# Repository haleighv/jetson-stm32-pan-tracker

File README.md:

# Jetson Orin + STM32H7 closed-loop visual tracker

> Status: in progress (started October 2026).

A camera mounted to a motor for visually tracking and centering an AprilTag (pan-only).

Vision in ROS 2 runs on a **Jetson Orin Nano**, while an **STM32H723** controls a geared DC motor in a 1 kHz closed loop. The real-time MCU communicates with the Jetson via **CAN**, with bulk telemetry handled over **Ethernet**. The motor control loop runs independently of the Linux and ROS 2 timing on the Jetson, and disables the motor if the Jetson stops responding.

Safety:
- hardware e-stop
- firmware state machine
- heartbeat timeout
- current limiting
- watchdog timer

## Progress
- [x] Jetson: JetPack 7.2.1 + ROS 2 Jazzy, IMX219 at 720p60 (59.77 fps, 0 dropped over ~68 s)
- [x] PID controller with host unit tests (anti-windup, no derivative kick, NaN-safe config)
- [x] STM32 bring-up: 520 MHz, FreeRTOS, task table, queued leveled logging, UART CLI
- [x] STM32 task framework: pub/sub messaging, startup sync, supervisor skeleton, LED task
- [x] 1 kHz control tick on TIM6: ±153 ns jitter under load (DWT min/max)
- [x] Jitter p99 from a Saleae capture: 77 ns idle, 34 ns loaded (crystal clock)
- [x] FDCAN internal loopback: 1M frames, 0 lost, 0 errors
- [x] CI: host tests + firmware build on every push, elf/map kept per commit
- [x] CAN bus to the Jetson at 1 Mbps: both directions, 0 errors
- [x] Motor open loop: VNH5019 driver, encoder, current sense, latched fault interrupt, brake on stop (220 RPM at full duty, stops in ~37 ms)
- [x] Motor driven from the 1 kHz control tick: single writer, lock-free task requests, 2 ms reversal brake, ~2 µs per tick
- [x] Custom Nucleo shield (Nuc-hatch rev A): designed in KiCad, ordered assembled from JLCPCB
- [ ] Motor closed loop: velocity and position
- [ ] Safety: e-stop, heartbeat, watchdog
- [ ] ROS 2 tracking pipeline
- [ ] Measured results

## Demo
Coming soon

## Results
| Metric | Target (Day 0 estimate) | Measured |
|---|---|---|
| Photon-to-motion latency, p50 / p90 | < 60 / 80 ms | TBD |
| Control-loop period jitter, p99 | < 2 µs | 77 ns idle, 34 ns loaded (Saleae, 90 s) |
| Step response (30°): rise time / overshoot | < 100 ms / < 10 % | TBD |
| Heartbeat-loss → motor disabled | ≤ 50 ms | TBD |

## Architecture (planned)
```mermaid
flowchart LR
  subgraph J[Jetson Orin Nano · JetPack 7.2.1 · ROS 2 Jazzy]
    CAM[camera node<br/>IMX219 720p60] --> TAG[apriltag node]
    TAG --> TRK[tracker node<br/>outer loop 60 Hz]
    TRK --> BR[can_bridge<br/>SocketCAN]
    LOG[telemetry logger]
  end
  BR -- "CAN 1 Mbps: setpoint, heartbeat, command" --> M
  M -- "CAN: status 100 Hz" --> BR
  M -- "UDP: 1 kHz telemetry" --> LOG
  subgraph M[NUCLEO-H723ZG · FreeRTOS]
    SAFE[safety state machine] --> CTL[pos→vel PID 1 kHz]
    CTL --> PWM[PWM 20 kHz + current limit]
    DBG[logs + CLI<br/>USART3]
  end
  PWM --> DRV[VNH5019] --> MOT[goBILDA 5203 gearmotor]
  MOT -- encoder --> CTL
  DRV -- current sense --> PWM
  ES[e-stop] -- "cuts 12 V" --> DRV
  ES -- sense --> SAFE
```

## Repo layout
```
firmware/
  lib/        portable C, host-tested (PID, CLI parser, LED fade)
  tests/      Unity host tests
  nucleo/     NUCLEO-H723ZG target: CubeMX BSP (Core/, Drivers/, .ioc) + app/
  scripts/    build.sh, test.sh (host), build_nucleo.sh, flash.sh (target)
ros2_ws/      ROS 2 packages (camera, apriltag, tracker, can_bridge)
hardware/     wiring, pinouts, CAD (STEP/3MF), photos
docs/         plan, worklog, firmware architecture, results/
tools/        analysis scripts (jitter, step response, latency)
```

## Build and test
Needs cmake, ninja, Arm GNU Toolchain (`arm-none-eabi-gcc`), and STM32CubeProgrammer (`STM32_Programmer_CLI` on PATH).

```
./firmware/scripts/test.sh            # host unit tests (PID, CLI, LED fade)
./firmware/scripts/flash.sh           # build + flash the Nucleo over ST-LINK
tio -b 1000000 /dev/cu.usbmodem*      # logs + CLI at 1 Mbaud, type ? for commands
python3 tools/motor_profile.py        # motor characterization suite (quit tio first)
```

CI (`.github/workflows/ci.yml`) runs the host tests and builds the firmware on every push to `mainline` and every PR. Each run keeps `nucleo.elf` and `nucleo.map` as a download. To flash one:
```
STM32_Programmer_CLI -c port=SWD -w nucleo.elf -v -rst
```

### Debugging in VS Code
Open the repo folder and install the recommended extensions when prompted (`.vscode/extensions.json`): Cortex-Debug, RTOS Views, STM32Cube for VS Code (provides the ST-LINK GDB server, STM32CubeProgrammer, and the STM32H7 device pack), CMake Tools.

| Key | Does |
|---|---|
| `Cmd + Shift + B` | Build the Nucleo firmware (`.vscode/tasks.json`) |
| `F5` | Build, flash, debug, stop at `main()` (`.vscode/launch.json`, "Debug nucleo") |

"Attach nucleo" connects to a running board without reflashing or resetting, for looking at a hang or fault.

Tool versions the debug config expects: ST-LINK GDB server 7.14.0, STM32CubeProgrammer 2.23.0, STM32H7xx DFP 1.3.0 (paths under `~/Library/Application Support/stm32cube/`). If an extension update changes them, find the new paths with `mdfind -name ST-LINK_gdbserver` (and `STM32_Programmer_CLI`, `STM32H723.svd`) and update `launch.json`.

Optional shortcuts, in your own keybindings (`Cmd + Shift + P` → Preferences: Open Keyboard Shortcuts (JSON)):
```json
{ "key": "f6",          "command": "workbench.action.tasks.runTask", "args": "flash nucleo" },
{ "key": "cmd+shift+t", "command": "workbench.action.tasks.runTask", "args": "host tests" }
```
`F6` replaces VS Code's "Focus Next Part" and `Cmd + Shift + T` replaces "Reopen Closed Editor".

## Docs
- [Plan](docs/plan.md): milestones, results targets, scope
- [Worklog](docs/worklog.md): day-by-day progress
- [Firmware architecture](docs/firmware-architecture.md): tasks, priorities, logging, memory
- [Results](docs/results/): raw measurements
- [CAN wiring](hardware/can-wiring.md): bus layout, pins on both ends, checks
- [CAD](hardware/cad/): 3D-printed enclosure for the motor driver (STEP, 3MF)
- [Pinouts](hardware/pinouts.html): Nucleo Zio headers and Jetson 40-pin, with this project's pins marked (open locally in a browser)

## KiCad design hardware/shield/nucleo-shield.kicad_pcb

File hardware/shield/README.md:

# Nuc-hatch: Nucleo-H723ZG shield, rev A

A shield for the NUCLEO-H723ZG that replaces the hand-soldered jumper hub: CAN module socket, VNH5019 and encoder headers, sensor and end-of-travel inputs, an e-stop with a hardware path to the driver's EN line, and a breakout header that can cut and probe every signal. All through-hole, 2.54 mm headers, 2 layers.

Status: routed (Freerouting, then cleaned up in KiCad 10). ERC clean. DRC clean, with three courtyard overlaps excluded (Nucleo mounting holes next to the Zio rows, as on the Nucleo itself). Ordered 2026-11-18 from JLCPCB: 5 boards, fully assembled (top and bottom). Not tested yet.

## Files

| File | What |
|---|---|
| `nucleo-shield.kicad_pro`, `.kicad_sch`, `.kicad_pcb` | KiCad project, now saved by KiCad 10. |
| `gen/spec.py` | Source of truth: parts, nets, footprints, placement. |
| `gen/gen_sch.py`, `gen/gen_pcb.py`, `gen/gen_bom.py` | Generate the schematic, the placed board and `BOM.csv` from the spec. |
| `gen/check_net.py` | Compares the schematic's netlist with the spec. |
| `nucleo-shield-top.png`, `nucleo-shield-bottom.png` | KiCad 3D renders of the routed board. |
| `schematic.pdf` | Schematic. |
| `fit-check-1to1.pdf` | Copper, silkscreen and outline at 1:1, for the paper fit check. |
| `art/nuc-hatch-silk.png`, `art/nuc-hatch-pixel-art.png` | Nuthatch logo: 1-bit silkscreen image (0.5 mm per pixel, 24.5 x 11 mm) and the colour pixel art it came from. |
| `BOM.csv` | Parts list, with the LCSC part numbers used for the JLCPCB assembly. |
| `nucleo-shield-revA-gerbers.zip` | Gerbers and drill files as ordered (KiCad 10 plot, Protel extensions). |
| `jlc/nucleo-shield-revA-bom-jlc.csv`, `jlc/nucleo-shield-revA-cpl-jlc.csv` | JLCPCB assembly BOM and placement. CN7-CN10 are bottom side; C2 and C3 are not fitted. |

Once the board is routed in KiCad, the KiCad files are the source; the generators are for rev A only.

## Zio geometry

- The Nucleo's mounting holes are the Arduino Uno holes (UM2407 Figure 6: 48.26, 50.80 and 15.24 mm spacings), so the Arduino rows come from KiCad's `Module:Arduino_UNO_R3`.
- Each Zio connector adds a second row one 2.54 mm column inward. Left side: odd pins outer. Right side: even pins outer. Pin 1 at the ST-LINK end.
- CN7 sits 4.06 mm off the 2.54 mm grid from CN10 (the Arduino D7/D8 gap). CN9 and CN10 end on the same row.
- Origin in `spec.py` is CN8 pin 1. Holes at (0, -13.97), (48.26, -12.70), (33.02, 38.10), (1.27, 62.23), (46.99, 62.23).

## Connectors

| Ref | Name | Pins | Goes to |
|---|---|---|---|
| J1 | MOTOR | 3V3, GND, INA, INB, PWM, ENA, ENB, CS | VNH5019 carrier logic side. ENA and ENB are tied on the board. |
| J2 | ENCODER | GND, 3V3, A, B | goBILDA 5203 encoder, through the breakout and R2/R3 (100 Ω) to PD12/PD13 |
| J3 | CAN | 3V3, GND, TX, RX | SN65HVD230 module (TX to its D, RX to its R) |
| J4 | HOME | 3V3, GND, SIG | Slot sensor, PD14 (TIM4 CH3, input capture) |
| J5, J6 | END+, END- | 3V3, GND, SIG | End-of-travel sensors, PF3 and PG1 |
| J7 | AUX | 3V3, GND, SIG | Spare, PD15 (TIM4 CH4) |
| J8 | ESTOP | SW, GND | Normally closed e-stop switch, PG12 through R5 |
| J9 | BREAKOUT | 2x15, left: device side, right: MCU side | One row per signal: ESTOP, HOME, END+, END-, AUX, PWM, INA, INB, EN, CS, ENC A, ENC B, CAN TX, CAN RX, SCOPE (PG14, both pins). A shunt across each row makes the normal connection. |
| J10 | POWER | 5V, 3V3, GND, GND | Meter and spare power |
| J11-J14 | GND | 2 pins each | Probe grounds, one in each corner |
| JP1, JP2 | STOP END+/- | shunt | Shunt fitted: that end sensor also cuts EN in hardware |

Motor current sense: R1 1 kΩ and C1 100 nF between the breakout's CS row and PF4 (corner about 1.6 kHz), same as the hub.

## Breakout

- Normal running: a shunt on all 14 signal rows (SCOPE needs none).
- Pull a shunt to isolate a device from the Nucleo, then probe either side, or drive the Nucleo side from outside.
- Open-top (tall) shunts leave the pin tips exposed, so probe hooks can clip on with the shunt fitted.
- With a shunt pulled, that Nucleo input floats unless firmware turns on its pull-up.

## Hardware stop

- The e-stop switch (normally closed) holds ESTOP_SW low. An open switch or a broken wire lets R4 pull it high.
- ESTOP_SW and the end sensors (high when blocked, through JP1/JP2) are diode-ORed (D1-D3) into Q1's base. Q1 pulls EN low, the VNH5019 turns off, and the firmware sees the line low with EN released, which latches the motor fault.
- The whole stop path sits on the device side of the breakout, so it still works with the breakout shunts pulled.
- R7 keeps Q1 off when every input is low.
- No e-stop wired: put a shunt on J8, or the driver stays off.

## Before ordering

1. Run ERC and DRC. Expected: clean, with the three courtyard overlaps between Zio headers and Nucleo mounting holes excluded.
2. Print `fit-check-1to1.pdf` at 100% (no fit-to-page), check the scale with a ruler, push the paper onto the Nucleo's Zio sockets, and check every pin lines up.
3. Check the J1 order against the Pololu carrier's silkscreen. I wire it with jumpers, so the order only has to match the labels.
4. Zio sockets need male headers with standard 6 mm mating pins. CN7-CN10 go in from the bottom (plastic under the board, long pins down; outlines and labels are on the bottom silkscreen) and solder on top. Solder them with the shield plugged into the Nucleo so they come out straight. Their footprints differ from the library copies for this reason (DRC warning excluded).

## Routing

- Freerouting (KiCad Plugin and Content Manager), then the session imported and fixed by hand: two GND pins on CN10 tied back to the pour.
- Rules: 0.3 mm tracks, 0.2 mm clearance, 0.6/0.3 mm vias. Relaxed to fab limits where the router squeezed: 0.15 mm minimum track (four short necks), 0.3 mm copper to edge, one thermal spoke allowed on crowded GND header pins.
- +3V3 ended up at 0.3 mm (0.225 mm in places): the Power net class pattern was `+3V3` but KiCad names the net `/+3V3`, so it never applied. Fine for the ~100 mA on 3.3 V.

## Regenerate

```
cd hardware/shield/gen
python3 gen_sch.py ../nucleo-shield.kicad_sch
python3 gen_pcb.py place ../nucleo-shield.kicad_pcb
python3 gen_bom.py > ../BOM.csv
```

`gen_pcb.py` overwrites the board, routing included. Needs KiCad's Python module (`pcbnew`) and `sexpdata`.

Author: Haleigh (haleighv). Copyright (c) 2026 haleighv. SPDX-License-Identifier: MIT

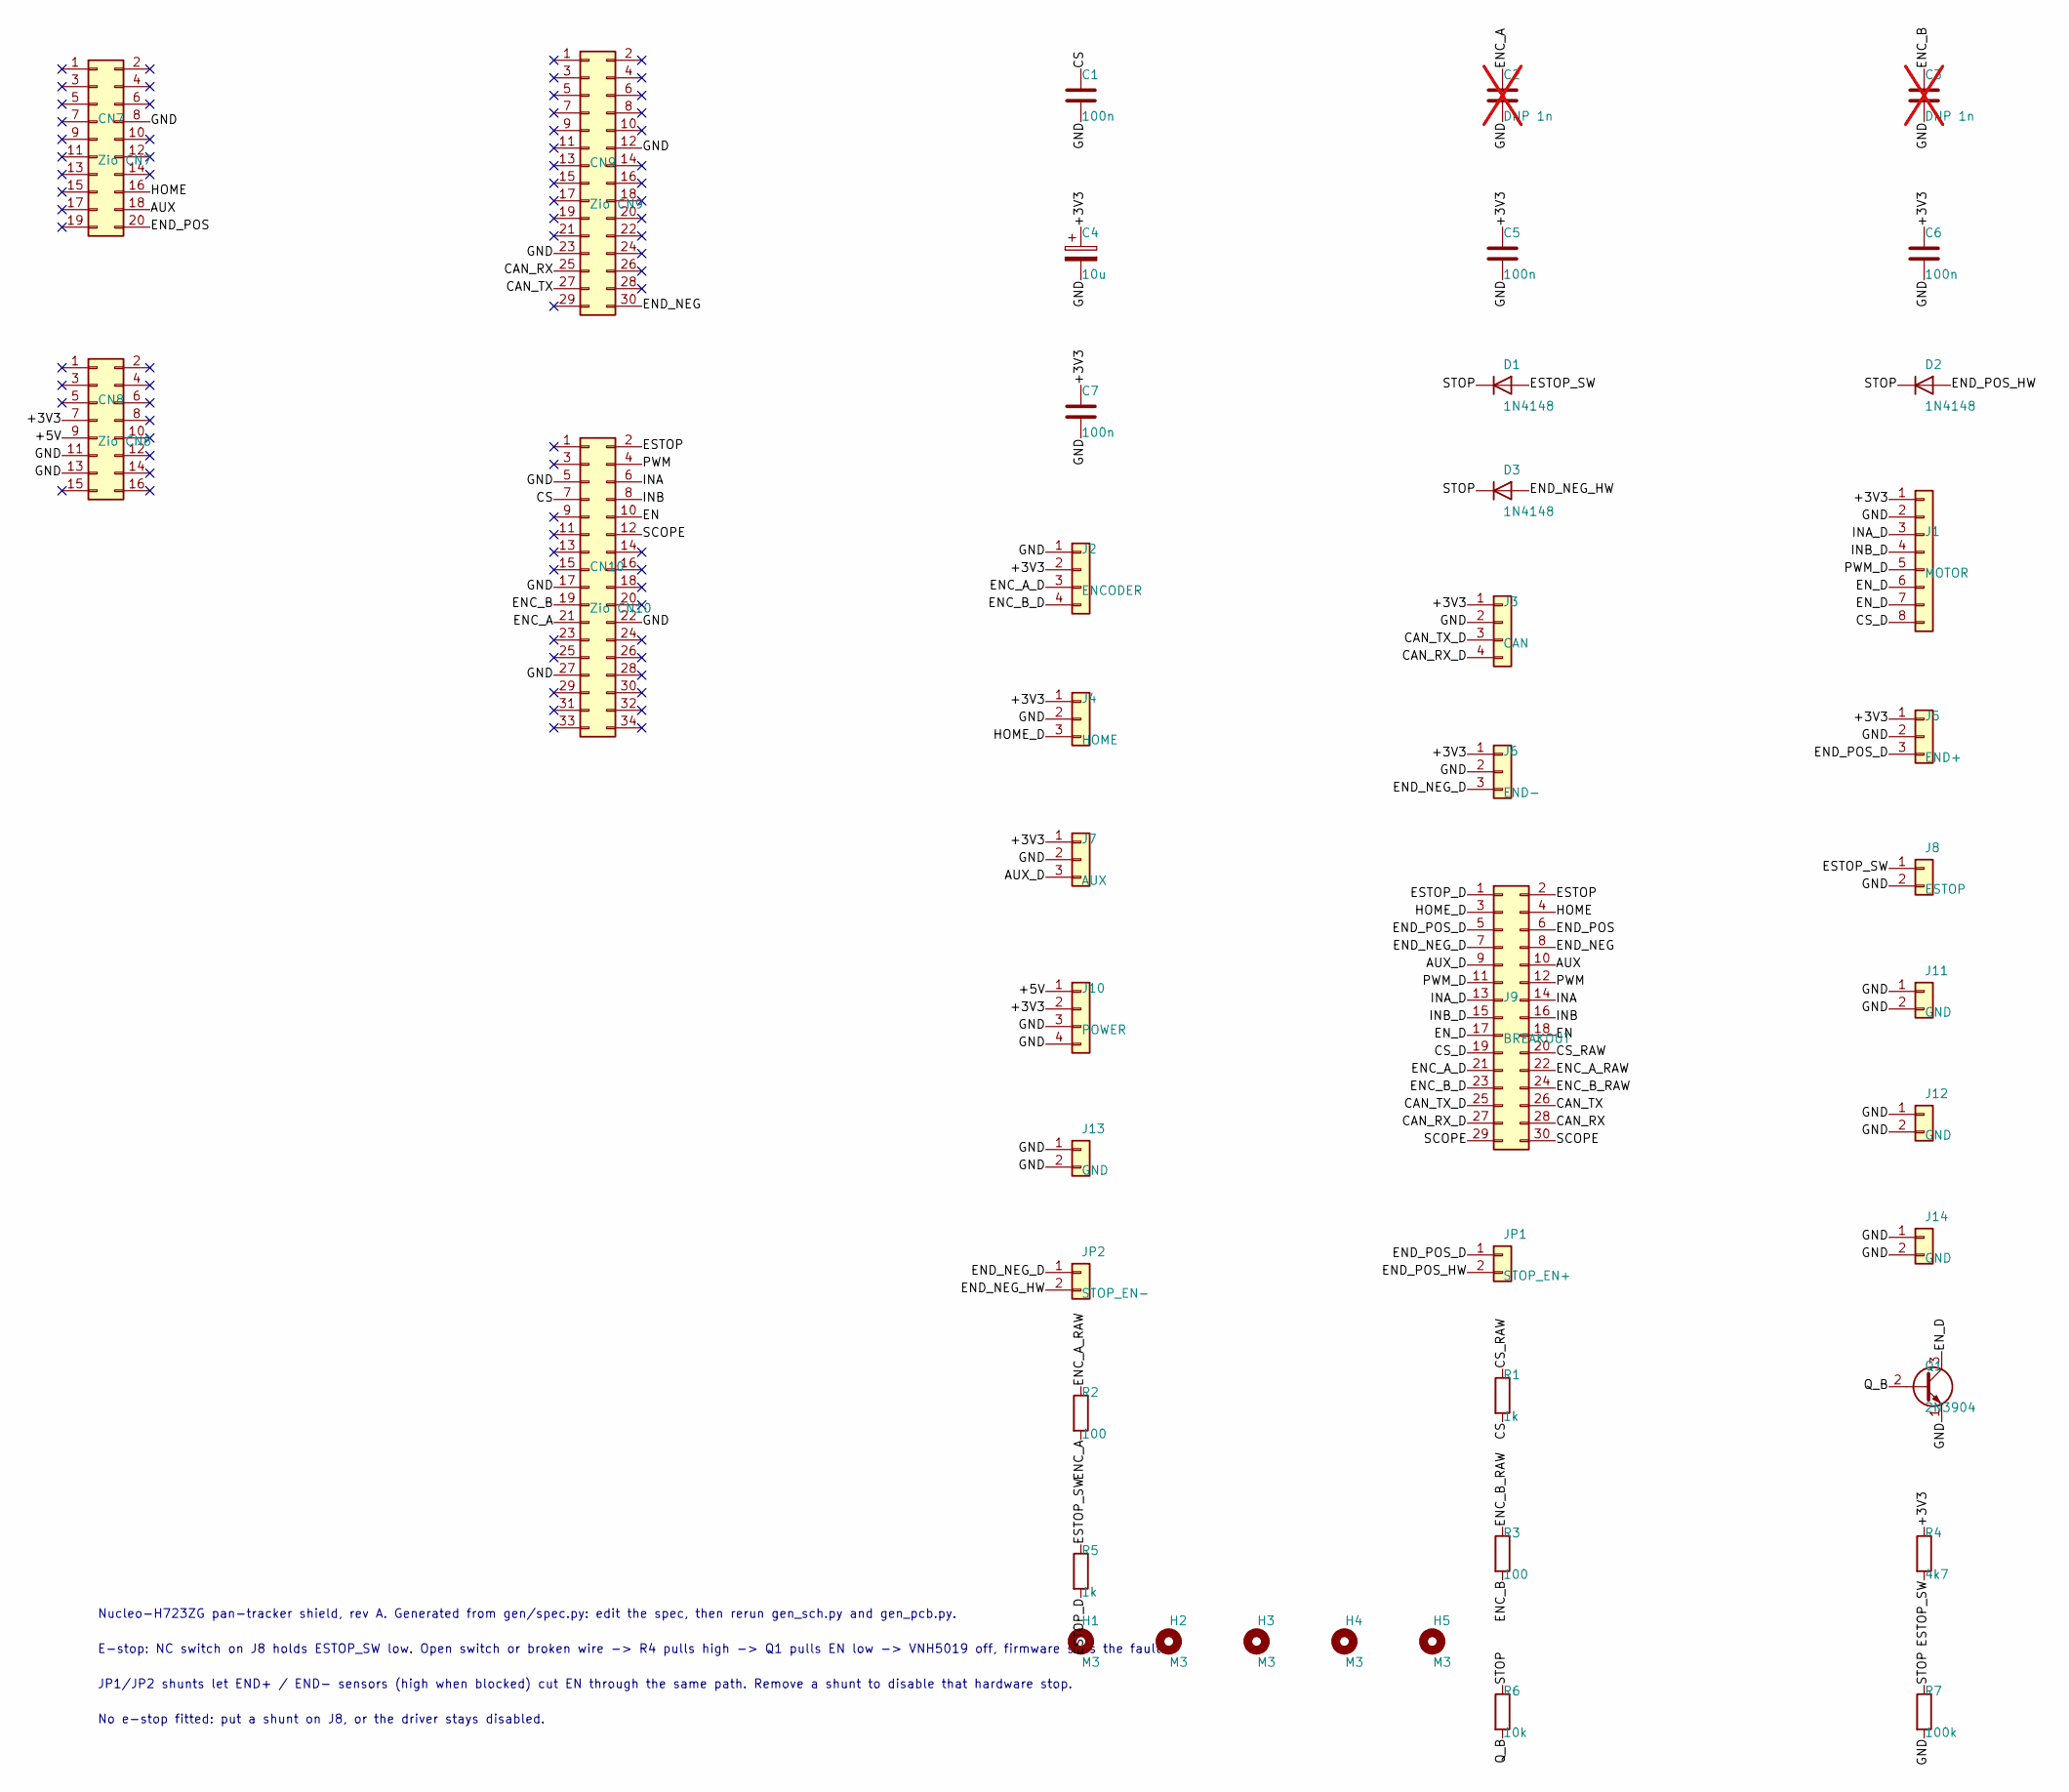
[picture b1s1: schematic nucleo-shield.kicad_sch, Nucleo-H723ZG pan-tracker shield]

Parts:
C1, C5, C6, C7: 100n; C_Disc_D5.0mm_W2.5mm_P5.00mm
C2, C3: DNP 1n; C_Disc_D5.0mm_W2.5mm_P5.00mm; not fitted
C4: 10u; CP_Radial_D5.0mm_P2.00mm
CN7: Zio CN7; PinHeader_2x10_P2.54mm_Vertical
CN8: Zio CN8; PinHeader_2x08_P2.54mm_Vertical
CN9: Zio CN9; PinHeader_2x15_P2.54mm_Vertical
CN10: Zio CN10; PinHeader_2x17_P2.54mm_Vertical
D1, D2, D3: 1N4148; D_DO-35_SOD27_P7.62mm_Horizontal
H1, H2, H3, H4, H5: M3; MountingHole_3.2mm_M3
J1: MOTOR; PinHeader_1x08_P2.54mm_Vertical
J2: ENCODER; PinHeader_1x04_P2.54mm_Vertical
J3: CAN; PinHeader_1x04_P2.54mm_Vertical
J4: HOME; PinHeader_1x03_P2.54mm_Vertical
J5: END+; PinHeader_1x03_P2.54mm_Vertical
J6: END-; PinHeader_1x03_P2.54mm_Vertical
J7: AUX; PinHeader_1x03_P2.54mm_Vertical
J8: ESTOP; PinHeader_1x02_P2.54mm_Vertical
J9: BREAKOUT; PinHeader_2x15_P2.54mm_Vertical
J10: POWER; PinHeader_1x04_P2.54mm_Vertical
J11, J12, J13, J14: GND; PinHeader_1x02_P2.54mm_Vertical
JP1: STOP_EN+; PinHeader_1x02_P2.54mm_Vertical
JP2: STOP_EN-; PinHeader_1x02_P2.54mm_Vertical
Q1: 2N3904; TO-92_Inline
R1, R5: 1k; R_Axial_DIN0207_L6.3mm_D2.5mm_P10.16mm_Horizontal
R2, R3: 100; R_Axial_DIN0207_L6.3mm_D2.5mm_P10.16mm_Horizontal
R4: 4k7; R_Axial_DIN0207_L6.3mm_D2.5mm_P10.16mm_Horizontal
R6: 10k; R_Axial_DIN0207_L6.3mm_D2.5mm_P10.16mm_Horizontal
R7: 100k; R_Axial_DIN0207_L6.3mm_D2.5mm_P10.16mm_Horizontal

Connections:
/+3V3: C4.1, C5.1, C6.1, C7.1, CN8.7, J1.1, J2.2, J3.1, J4.1, J5.1, J6.1, J7.1, J10.2, R4.1
/+5V: CN8.9, J10.1
/AUX: CN7.18, J9.10
/AUX_D: J7.3, J9.9
/CAN_RX: CN9.25, J9.28
/CAN_RX_D: J3.4, J9.27
/CAN_TX: CN9.27, J9.26
/CAN_TX_D: J3.3, J9.25
/CS: C1.1, CN10.7, R1.2
/CS_D: J1.8, J9.19
/CS_RAW: J9.20, R1.1
/EN: CN10.10, J9.18
/ENC_A: C2.1, CN10.21, R2.2
/ENC_A_D: J2.3, J9.21
/ENC_A_RAW: J9.22, R2.1
/ENC_B: C3.1, CN10.19, R3.2
/ENC_B_D: J2.4, J9.23
/ENC_B_RAW: J9.24, R3.1
/END_NEG: CN9.30, J9.8
/END_NEG_D: J6.3, J9.7, JP2.1
/END_NEG_HW: D3.2 (A), JP2.2
/END_POS: CN7.20, J9.6
/END_POS_D: J5.3, J9.5, JP1.1
/END_POS_HW: D2.2 (A), JP1.2
/EN_D: J1.6, J1.7, J9.17, Q1.3 (C)
/ESTOP: CN10.2, J9.2
/ESTOP_D: J9.1, R5.2
/ESTOP_SW: D1.2 (A), J8.1, R4.2, R5.1
/GND: C1.2, C2.2, C3.2, C4.2, C5.2, C6.2, C7.2, CN7.8, CN8.11, CN8.13, CN9.12, CN9.23, CN10.5, CN10.17, CN10.22, CN10.27, J1.2, J2.1, J3.2, J4.2, J5.2, J6.2, J7.2, J8.2, J10.3, J10.4, J11.1, J11.2, J12.1, J12.2, J13.1, J13.2, J14.1, J14.2, Q1.1 (E), R7.2
/HOME: CN7.16, J9.4
/HOME_D: J4.3, J9.3
/INA: CN10.6, J9.14
/INA_D: J1.3, J9.13
/INB: CN10.8, J9.16
/INB_D: J1.4, J9.15
/PWM: CN10.4, J9.12
/PWM_D: J1.5, J9.11
/Q_B: Q1.2 (B), R6.2
/SCOPE: CN10.12, J9.29, J9.30
/STOP: D1.1 (K), D2.1 (K), D3.1 (K), R6.1, R7.1

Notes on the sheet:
E-stop: NC switch on J8 holds ESTOP_SW low. Open switch or broken wire -> R4 pulls high -> Q1 pulls EN low -> VNH5019 off, firmware sees the fault.
Nucleo-H723ZG pan-tracker shield, rev A. Generated from gen/spec.py: edit the spec, then rerun gen_sch.py and gen_pcb.py.
No e-stop fitted: put a shunt on J8, or the driver stays disabled.
JP1/JP2 shunts let END+ / END- sensors (high when blocked) cut EN through the same path. Remove a shunt to disable that hardware stop.

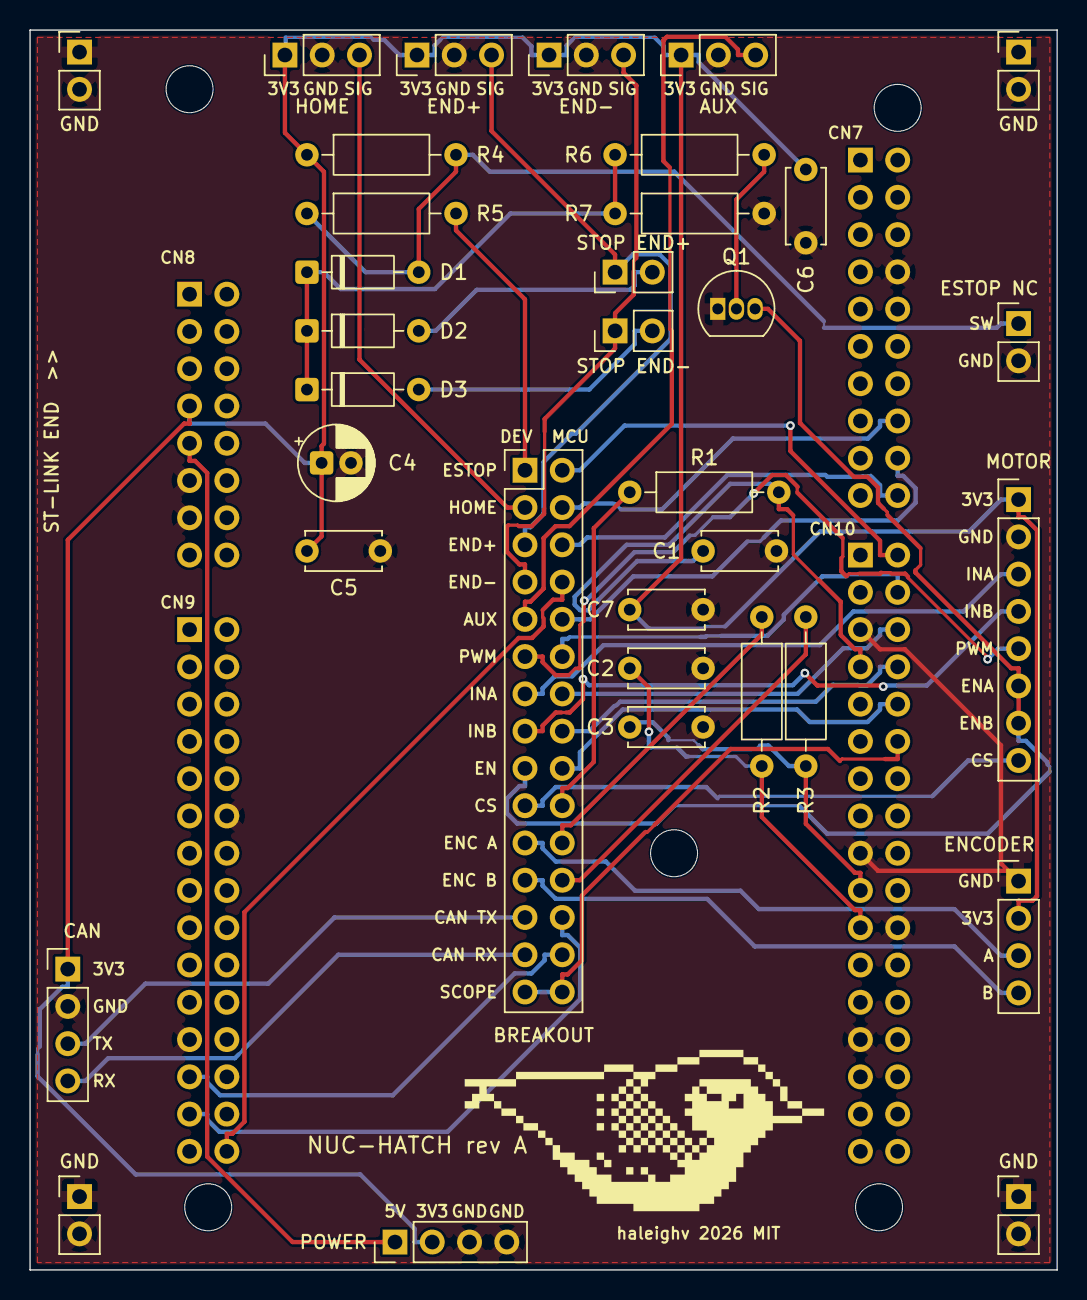
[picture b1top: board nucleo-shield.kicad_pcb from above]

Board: 2 copper layers, 70.0 x 84.5 mm, 43 parts (0 on the bottom side), 40 nets.

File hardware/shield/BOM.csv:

Qty,Refs,Value,Footprint,LCSC,Notes
4,C1 C5 C6 C7,100n,C_Disc_D5.0mm_W2.5mm_P5.00mm,C2167231,
2,C2 C3,DNP 1n,C_Disc_D5.0mm_W2.5mm_P5.00mm,,
1,C4,10u,CP_Radial_D5.0mm_P2.00mm,C88807,
1,CN7,"Male header 2x10, 2.54 mm (pins down into Zio)",PinHeader_2x10_P2.54mm_Vertical,C124359,
1,CN8,"Male header 2x8, 2.54 mm (pins down into Zio)",PinHeader_2x08_P2.54mm_Vertical,C124389,
1,CN9,"Male header 2x15, 2.54 mm (pins down into Zio)",PinHeader_2x15_P2.54mm_Vertical,C42372523,
1,CN10,"Male header 2x17, 2.54 mm (pins down into Zio)",PinHeader_2x17_P2.54mm_Vertical,C19630945,
3,D1 D2 D3,1N4148,D_DO-35_SOD27_P7.62mm_Horizontal,C84410,
1,J1,"Male header 1x8, 2.54 mm",PinHeader_1x08_P2.54mm_Vertical,C124381,VNH5019 carrier logic: VDD GND INA INB PWM ENA ENB CS
1,J2,"Male header 1x4, 2.54 mm",PinHeader_1x04_P2.54mm_Vertical,C124378,goBILDA 5203 encoder
1,J3,"Male header 1x4, 2.54 mm",PinHeader_1x04_P2.54mm_Vertical,C124378,SN65HVD230 module: VCC GND TX(D) RX(R)
1,J4,"Male header 1x3, 2.54 mm",PinHeader_1x03_P2.54mm_Vertical,C124376,Slot sensor
1,J5,"Male header 1x3, 2.54 mm",PinHeader_1x03_P2.54mm_Vertical,C124376,"End of travel, positive"
1,J6,"Male header 1x3, 2.54 mm",PinHeader_1x03_P2.54mm_Vertical,C124376,"End of travel, negative"
1,J7,"Male header 1x3, 2.54 mm",PinHeader_1x03_P2.54mm_Vertical,C124376,Spare sensor input
1,J8,"Male header 1x2, 2.54 mm",PinHeader_1x02_P2.54mm_Vertical,C32713268,NC switch; fit a shunt if no e-stop
1,J9,"Male header 2x15, 2.54 mm",PinHeader_2x15_P2.54mm_Vertical,C42372523,Shunt per row: device side (odd) to MCU side (even)
1,J10,"Male header 1x4, 2.54 mm",PinHeader_1x04_P2.54mm_Vertical,C124378,Meter and spare power
1,J11,"Male header 1x2, 2.54 mm",PinHeader_1x02_P2.54mm_Vertical,C32713268,"Probe ground, top left"
1,J12,"Male header 1x2, 2.54 mm",PinHeader_1x02_P2.54mm_Vertical,C32713268,"Probe ground, top right"
1,J13,"Male header 1x2, 2.54 mm",PinHeader_1x02_P2.54mm_Vertical,C32713268,"Probe ground, bottom left"
1,J14,"Male header 1x2, 2.54 mm",PinHeader_1x02_P2.54mm_Vertical,C32713268,"Probe ground, bottom right"
1,JP1,"Male header 1x2, 2.54 mm",PinHeader_1x02_P2.54mm_Vertical,C32713268,Shunt: END+ cuts EN in hardware; fit a 2.54 mm shunt
1,JP2,"Male header 1x2, 2.54 mm",PinHeader_1x02_P2.54mm_Vertical,C32713268,Shunt: END- cuts EN in hardware; fit a 2.54 mm shunt
1,Q1,2N3904,TO-92_Inline,C118538,Pulls EN low: VNH5019 off
2,R1 R5,1k,R_Axial_DIN0207_L6.3mm_D2.5mm_P10.16mm_Horizontal,C57435,
2,R2 R3,100,R_Axial_DIN0207_L6.3mm_D2.5mm_P10.16mm_Horizontal,C57438,
1,R4,4k7,R_Axial_DIN0207_L6.3mm_D2.5mm_P10.16mm_Horizontal,C57204,
1,R6,10k,R_Axial_DIN0207_L6.3mm_D2.5mm_P10.16mm_Horizontal,C57436,
1,R7,100k,R_Axial_DIN0207_L6.3mm_D2.5mm_P10.16mm_Horizontal,C58597,

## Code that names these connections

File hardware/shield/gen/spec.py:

"""
spec.py

Single source of truth for the Nucleo-H723ZG pan-tracker shield, rev A:
parts, footprints, nets and placement. gen_sch.py and gen_pcb.py both read
this, so the schematic and the board can't disagree.

Coordinates (board, mm): X across the board, Y along it, Y grows away from
the ST-LINK end. Origin = CN8 pin 1 (Arduino power header pin 1).
Zio geometry: Arduino rows from KiCad Module:Arduino_UNO_R3, extra Zio rows
one 2.54 mm column inward. Left side: odd pins outer (X 0). Right side: even
pins outer (X 48.26). Checked against UM2407 Rev 6 Figure 6 (hole spacing
48.26, 50.80, 15.24 mm; CN9 and CN10 last rows level).

Author: Haleigh (haleighv)
Copyright (c) 2026 haleighv
SPDX-License-Identifier: MIT
"""

P = 2.54

# Zio connectors: ref -> (pins, X of pad 1, Y of pad 1). Pad 2 is at X + 2.54.
ZIO = {
    "CN8":  (16, 0.0,   0.0),     # odd outer (Arduino power), even inner
    "CN9":  (30, 0.0,  22.86),    # odd outer (Arduino A0-A5), even inner
    "CN7":  (20, 45.72, -9.14),   # odd inner, even outer (Arduino D8-D15)
    "CN10": (34, 45.72, 17.78),   # odd inner, even outer (Arduino D0-D7)
}

# Nucleo-144 mounting holes under the Zio area (M3), board coords.
HOLES = [(0.0, -13.97), (48.26, -12.70), (33.02, 38.10), (1.27, 62.23), (46.99, 62.23)]

# Board outline: same width as the Nucleo (70 mm), clear of ST-LINK jumpers
# and the RJ45.
OUTLINE = (-10.87, -18.0, 59.13, 66.5)   # x0, y0, x1, y1

# Zio pin -> net. Unlisted pins are left unconnected (no-connect).
ZIO_NETS = {
    # power
    "CN8-7": "+3V3", "CN8-9": "+5V",
    "CN7-8": "GND", "CN8-11": "GND", "CN8-13": "GND", "CN9-12": "GND",
    "CN9-23": "GND", "CN10-5": "GND", "CN10-17": "GND", "CN10-22": "GND",
    "CN10-27": "GND",
    # motor (VNH5019 carrier)
    "CN10-4": "PWM",      # PE9  TIM1_CH1
    "CN10-6": "INA",      # PE11
    "CN10-8": "INB",      # PE14
    "CN10-10": "EN",      # PE13 open drain, ENA/ENB tied
    "CN10-7": "CS",       # PF4  ADC3_INP9, after the RC filter
    # encoder
    "CN10-21": "ENC_A",   # PD12 TIM4_CH1
    "CN10-19": "ENC_B",   # PD13 TIM4_CH2
    # CAN module
    "CN9-25": "CAN_RX",   # PD0 FDCAN1_RX
    "CN9-27": "CAN_TX",   # PD1 FDCAN1_TX
    # debug
    "CN10-12": "SCOPE",   # PG14 control tick toggle
    # sensors and stops
    "CN7-16": "HOME",     # PD14 TIM4_CH3
    "CN7-18": "AUX",      # PD15 TIM4_CH4
    "CN7-20": "END_POS",  # PF3
    "CN9-30": "END_NEG",  # PG1
    "CN10-2": "ESTOP",    # PG12, through R5
}

# Parts: ref -> (lib_id, value, footprint, {pin: net}, (x, y, rot), note)
FP_R = "Resistor_THT:R_Axial_DIN0207_L6.3mm_D2.5mm_P10.16mm_Horizontal"
FP_C = "Capacitor_THT:C_Disc_D5.0mm_W2.5mm_P5.00mm"
FP_CP = "Capacitor_THT:CP_Radial_D5.0mm_P2.00mm"
FP_D = "Diode_THT:D_DO-35_SOD27_P7.62mm_Horizontal"
FP_Q = "Package_TO_SOT_THT:TO-92_Inline"
FP_H = "Connector_PinHeader_2.54mm:PinHeader_{r}x{n:02d}_P2.54mm_Vertical"
FP_HOLE = "MountingHole:MountingHole_3.2mm_M3"


def hdr(rows, n):
    return FP_H.format(r=rows, n=n)


# Breakout: one row per signal, device side in the left column (odd pins),
# MCU side in the right column (even pins). A shunt across a row makes the
# normal connection; pull it to isolate a device or probe either side.
BREAKOUT = [
    ("ESTOP", "ESTOP_D", "ESTOP"),
    ("HOME", "HOME_D", "HOME"),
    ("END+", "END_POS_D", "END_POS"),
    ("END-", "END_NEG_D", "END_NEG"),
    ("AUX", "AUX_D", "AUX"),
    ("PWM", "PWM_D", "PWM"),
    ("INA", "INA_D", "INA"),
    ("INB", "INB_D", "INB"),
    ("EN", "EN_D", "EN"),
    ("CS", "CS_D", "CS_RAW"),
    ("ENC A", "ENC_A_D", "ENC_A_RAW"),
    ("ENC B", "ENC_B_D", "ENC_B_RAW"),
    ("CAN TX", "CAN_TX_D", "CAN_TX"),
    ("CAN RX", "CAN_RX_D", "CAN_RX"),
    ("SCOPE", "SCOPE", "SCOPE"),
]
J9_PINS = {}
for i, (_, dev, mcu) in enumerate(BREAKOUT):
    J9_PINS[2 * i + 1] = dev
    J9_PINS[2 * i + 2] = mcu

PARTS = {
    # --- off-board connectors (2.54 mm headers), all on the device side ---
    "J1": ("Connector_Generic:Conn_01x08", "MOTOR", hdr(1, 8),
           {1: "+3V3", 2: "GND", 3: "INA_D", 4: "INB_D", 5: "PWM_D", 6: "EN_D", 7: "EN_D", 8: "CS_D"},
           (56.5, 14.0, 0), "VNH5019 carrier logic: VDD GND INA INB PWM ENA ENB CS"),
    "J2": ("Connector_Generic:Conn_01x04", "ENCODER", hdr(1, 4),
           {1: "GND", 2: "+3V3", 3: "ENC_A_D", 4: "ENC_B_D"},
           (56.5, 40.0, 0), "goBILDA 5203 encoder"),
    "J3": ("Connector_Generic:Conn_01x04", "CAN", hdr(1, 4),
           {1: "+3V3", 2: "GND", 3: "CAN_TX_D", 4: "CAN_RX_D"},
           (-8.3, 46.0, 0), "SN65HVD230 module: VCC GND TX(D) RX(R)"),
    "J4": ("Connector_Generic:Conn_01x03", "HOME", hdr(1, 3),
           {1: "+3V3", 2: "GND", 3: "HOME_D"}, (6.5, -16.3, 90), "Slot sensor"),
    "J5": ("Connector_Generic:Conn_01x03", "END+", hdr(1, 3),
           {1: "+3V3", 2: "GND", 3: "END_POS_D"}, (15.5, -16.3, 90), "End of travel, positive"),
    "J6": ("Connector_Generic:Conn_01x03", "END-", hdr(1, 3),
           {1: "+3V3", 2: "GND", 3: "END_NEG_D"}, (24.5, -16.3, 90), "End of travel, negative"),
    "J7": ("Connector_Generic:Conn_01x03", "AUX", hdr(1, 3),
           {1: "+3V3", 2: "GND", 3: "AUX_D"}, (33.5, -16.3, 90), "Spare sensor input"),
    "J8": ("Connector_Generic:Conn_01x02", "ESTOP", hdr(1, 2),
           {1: "ESTOP_SW", 2: "GND"}, (56.5, 2.0, 0), "NC switch; fit a shunt if no e-stop"),
    "J9": ("Connector_Generic:Conn_02x15_Odd_Even", "BREAKOUT", hdr(2, 15), J9_PINS,
           (22.86, 12.0, 0), "Shunt per row: device side (odd) to MCU side (even)"),
    "J10": ("Connector_Generic:Conn_01x04", "POWER", hdr(1, 4),
            {1: "+5V", 2: "+3V3", 3: "GND", 4: "GND"}, (14.0, 64.6, 90), "Meter and spare power"),
    "J11": ("Connector_Generic:Conn_01x02", "GND", hdr(1, 2), {1: "GND", 2: "GND"},
            (-7.5, -16.5, 0), "Probe ground, top left"),
    "J12": ("Connector_Generic:Conn_01x02", "GND", hdr(1, 2), {1: "GND", 2: "GND"},
            (56.5, -16.5, 0), "Probe ground, top right"),
    "J13": ("Connector_Generic:Conn_01x02", "GND", hdr(1, 2), {1: "GND", 2: "GND"},
            (-7.5, 61.5, 0), "Probe ground, bottom left"),
    "J14": ("Connector_Generic:Conn_01x02", "GND", hdr(1, 2), {1: "GND", 2: "GND"},
            (56.5, 61.5, 0), "Probe ground, bottom right"),
    "JP1": ("Connector_Generic:Conn_01x02", "STOP_EN+", hdr(1, 2),
            {1: "END_POS_D", 2: "END_POS_HW"}, (29.0, -1.5, 90), "Shunt: END+ cuts EN in hardware"),
    "JP2": ("Connector_Generic:Conn_01x02", "STOP_EN-", hdr(1, 2),
            {1: "END_NEG_D", 2: "END_NEG_HW"}, (29.0, 2.5, 90), "Shunt: END- cuts EN in hardware"),
    # --- current sense filter (MCU side of the breakout) ---
    "R1": ("Device:R", "1k", FP_R, {1: "CS_RAW", 2: "CS"}, (30.0, 13.5, 0), "CS RC, ~1.6 kHz"),
    "C1": ("Device:C", "100n", FP_C, {1: "CS", 2: "GND"}, (35.0, 17.5, 0), "CS RC"),
    # --- encoder (series R, optional C), MCU side of the breakout ---
    "R2": ("Device:R", "100", FP_R, {1: "ENC_A_RAW", 2: "ENC_A"}, (39.0, 22.0, 270), "Series"),
    "R3": ("Device:R", "100", FP_R, {1: "ENC_B_RAW", 2: "ENC_B"}, (42.0, 22.0, 270), "Series"),
    "C2": ("Device:C", "DNP 1n", FP_C, {1: "ENC_A", 2: "GND"}, (30.0, 25.5, 0), "Optional"),
    "C3": ("Device:C", "DNP 1n", FP_C, {1: "ENC_B", 2: "GND"}, (30.0, 29.5, 0), "Optional"),
    # --- 3V3 bypass ---
    "C4": ("Device:C_Polarized", "10u", FP_CP, {1: "+3V3", 2: "GND"}, (9.0, 11.5, 0), "Bulk"),
    "C5": ("Device:C", "100n", FP_C, {1: "+3V3", 2: "GND"}, (8.0, 17.5, 0), "Bypass"),
    "C6": ("Device:C", "100n", FP_C, {1: "+3V3", 2: "GND"}, (42.0, -8.5, 270), "Bypass, sensors"),
    "C7": ("Device:C", "100n", FP_C, {1: "+3V3", 2: "GND"}, (30.0, 21.5, 0), "Bypass, motor"),
    # --- e-stop and hardware stop (device side, works with shunts pulled) ---
    "R4": ("Device:R", "4k7", FP_R, {1: "+3V3", 2: "ESTOP_SW"}, (8.0, -9.5, 0), "Pull-up: open switch = stop"),
    "R5": ("Device:R", "1k", FP_R, {1: "ESTOP_SW", 2: "ESTOP_D"}, (8.0, -5.5, 0), "Series to PG12"),
    "D1": ("Device:D", "1N4148", FP_D, {1: "STOP", 2: "ESTOP_SW"}, (8.0, -1.5, 0), "OR into STOP"),
    "D2": ("Device:D", "1N4148", FP_D, {1: "STOP", 2: "END_POS_HW"}, (8.0, 2.5, 0), "OR into STOP"),
    "D3": ("Device:D", "1N4148", FP_D, {1: "STOP", 2: "END_NEG_HW"}, (8.0, 6.5, 0), "OR into STOP"),
    "R6": ("Device:R", "10k", FP_R, {1: "STOP", 2: "Q_B"}, (29.0, -9.5, 0), "Base"),
    "R7": ("Device:R", "100k", FP_R, {1: "STOP", 2: "GND"}, (29.0, -5.5, 0), "Off when all inputs low"),
    "Q1": ("Transistor_BJT:2N3904", "2N3904", FP_Q, {1: "GND", 2: "Q_B", 3: "EN_D"}, (36.0, 1.0, 0),
           "Pulls EN low: VNH5019 off"),
}

MOUNTS = {f"H{i + 1}": xy for i, xy in enumerate(HOLES)}

# Net classes: power gets wide tracks.
POWER_NETS = {"+3V3", "+5V", "GND"}
